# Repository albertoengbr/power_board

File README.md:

# power_board
Breadbord power supply 3.3v e 5v

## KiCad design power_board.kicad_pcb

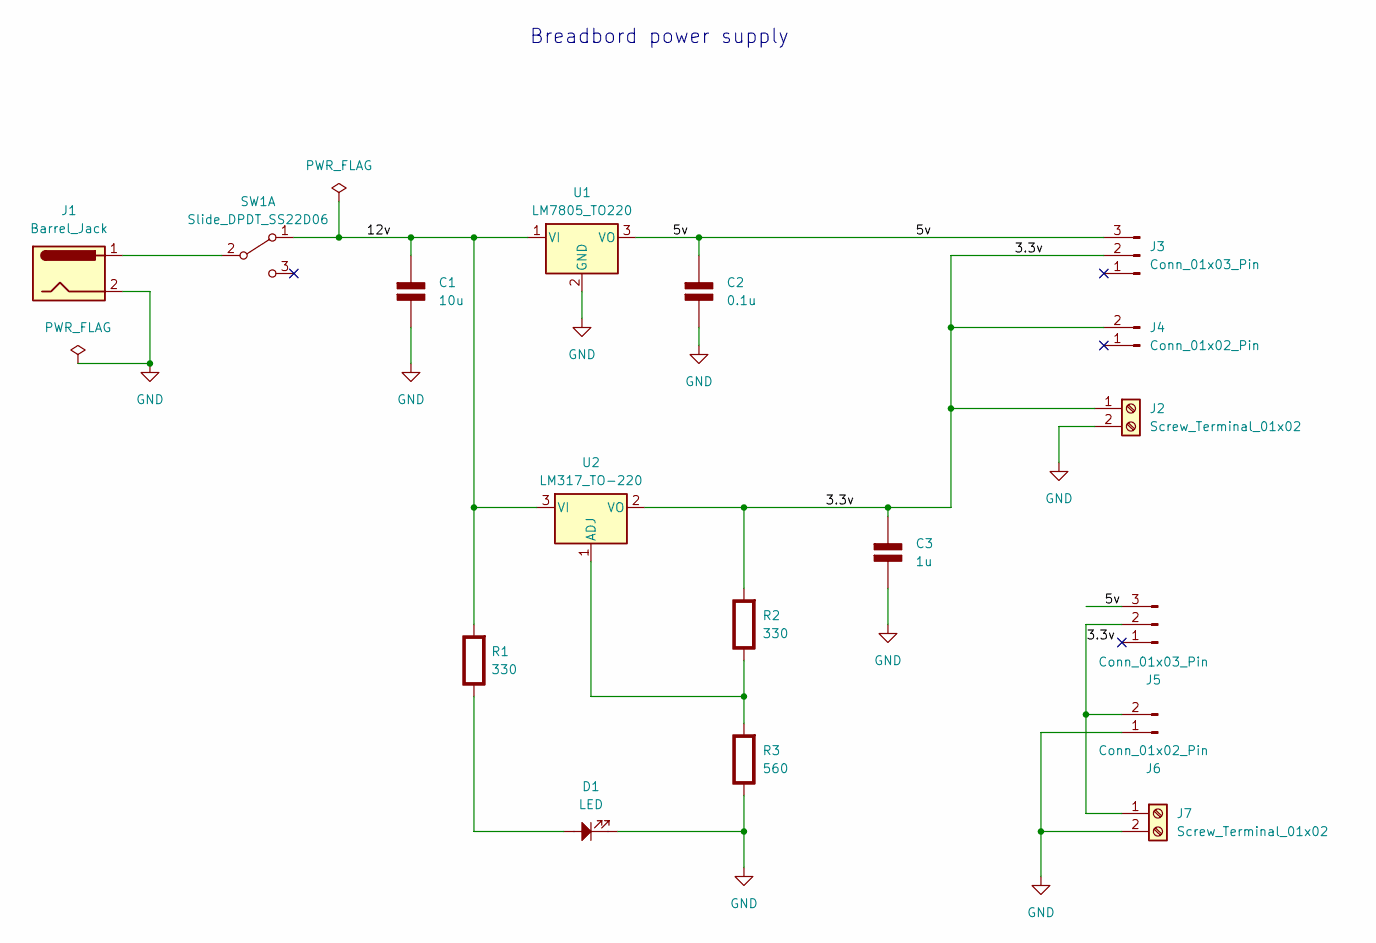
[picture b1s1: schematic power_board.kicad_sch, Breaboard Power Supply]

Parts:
C1: 10u; C_Disc_D3.8mm_W2.6mm_P2.50mm; Rating V
C2: 0.1u; C_Disc_D3.8mm_W2.6mm_P2.50mm; Rating V
C3: 1u; C_Disc_D3.8mm_W2.6mm_P2.50mm; Rating V
D1: LED; LED_D5.0mm
J1: Barrel_Jack; BarrelJack_Horizontal
J2, J7: Screw_Terminal_01x02; TerminalBlock_bornier-2_P5.08mm
J3, J5: Conn_01x03_Pin; PinSocket_1x03_P2.54mm_Vertical
J4, J6: Conn_01x02_Pin; PinSocket_1x02_P2.54mm_Vertical
R1, R2: 330; R_Axial_DIN0204_L3.6mm_D1.6mm_P1.90mm_Vertical; Rating W
R3: 560; R_Axial_DIN0204_L3.6mm_D1.6mm_P1.90mm_Vertical; Rating W
SW1: Slide_DPDT_SS22D06; Slide_Switch_Runrun_SS22D06; Part Number SS22D06
U1: LM7805_TO220; TO-220-3_Vertical
U2: LM317_TO-220; TO-220-3_Vertical

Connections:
/3.3v: C3.1 (+), J2.1, J3.2, J4.2, J5.2, J6.2, J7.1, R2.2 (-), U2.2 (VO)
/5v: C2.1 (+), J3.3, J5.3, U1.3 (VO)
/12v: C1.1 (+), R1.2 (-), SW1.1 (A), U1.1 (VI), U2.3 (VI)
GND: C1.2 (-), C2.2 (-), C3.2 (-), D1.1, J1.2, J2.2, J6.1, J7.2, R3.1 (+), U1.2 (GND)
unnamed: D1.2, R1.1 (+)
unnamed: R2.1 (+), R3.2 (-), U2.1 (ADJ)
unnamed: J1.1, SW1.2 (B)

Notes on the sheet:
Breadbord power supply

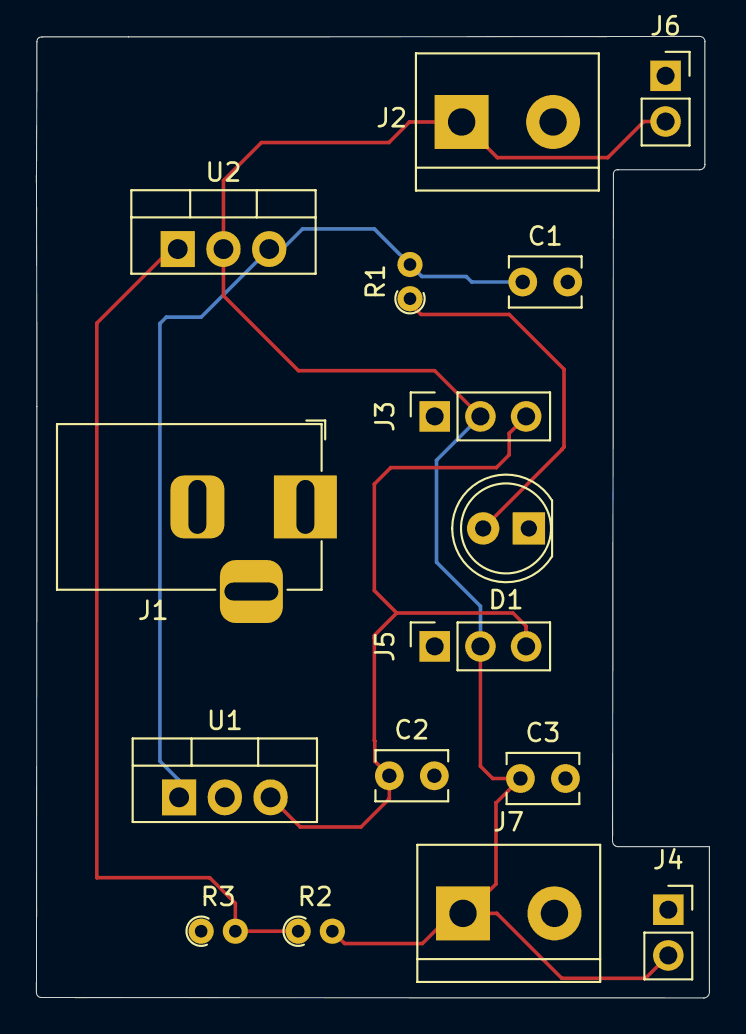
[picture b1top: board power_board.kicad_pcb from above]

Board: 2 copper layers, 37.4 x 53.4 mm, 16 parts (0 on the bottom side), 6 nets.

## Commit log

2025-01-01 Projeto Fonte 3v e 5v para placas Breadbord
2025-01-01 Adicionando todos os arquivos do diretório
